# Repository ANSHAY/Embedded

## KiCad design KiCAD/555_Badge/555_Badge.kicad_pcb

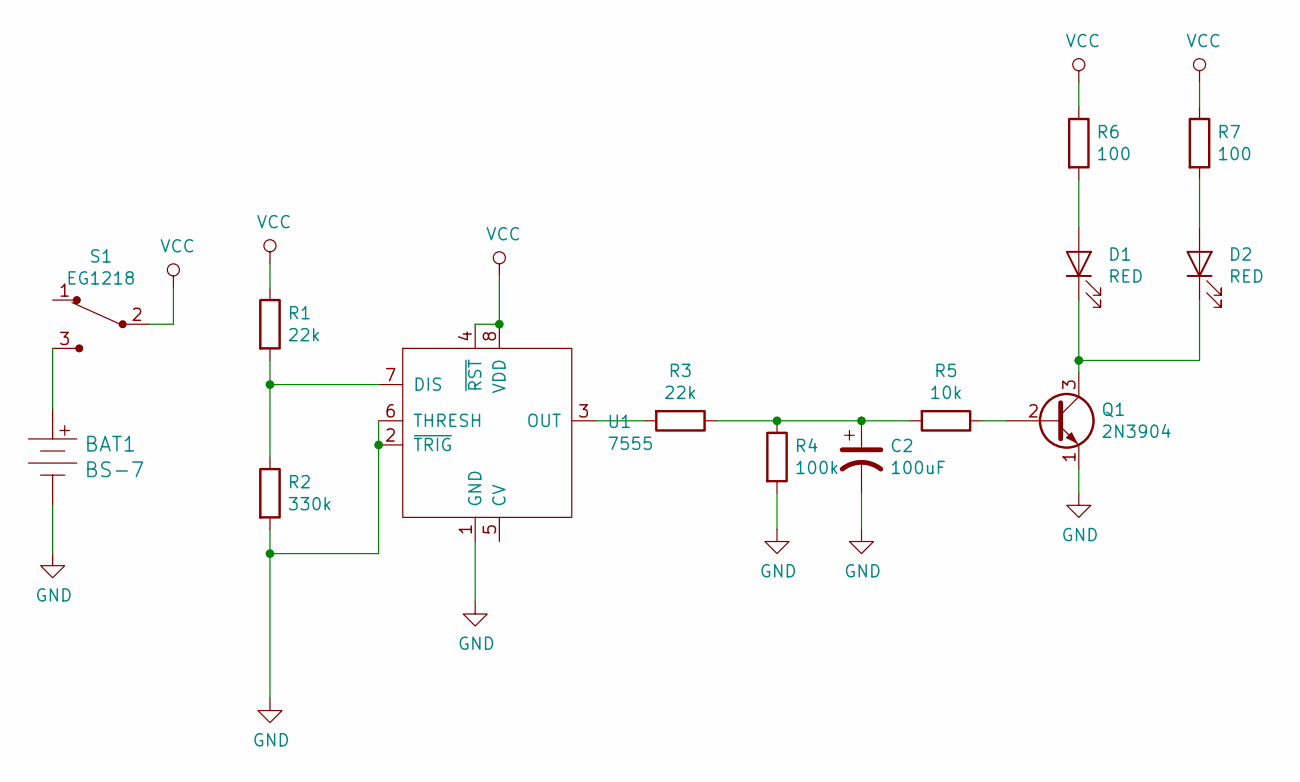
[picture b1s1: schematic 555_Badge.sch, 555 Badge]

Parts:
BAT1: BS-7; Battery_Holder_Coin_2032_BS-7; MPN BS-7; Digi-Key_PN BS-7-ND
C2: 100uF; CP_Radial_D6.3mm_P2.50mm
D1, D2: RED; LED_D3.0mm
Q1: 2N3904; TO-92-3
R1, R3: 22k; R_Axial_DIN0207_L6.3mm_D2.5mm_P7.62mm_Horizontal
R2: 330k; R_Axial_DIN0207_L6.3mm_D2.5mm_P7.62mm_Horizontal
R4: 100k; R_Axial_DIN0207_L6.3mm_D2.5mm_P7.62mm_Horizontal
R5: 10k; R_Axial_DIN0207_L6.3mm_D2.5mm_P7.62mm_Horizontal
R6, R7: 100; R_Axial_DIN0207_L6.3mm_D2.5mm_P7.62mm_Horizontal
S1: EG1218; Switch_Slide_11.6x4mm_EG1218; MPN EG1218; Digi-Key_PN EG1903-ND
U1: 7555; ICM7555-PDIP

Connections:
GND: BAT1.Neg, C2.2, Q1.1 (E), R2.2, R4.2, U1.1 (GND), U1.2 (~TRIG), U1.6 (THRESH)
unnamed: BAT1.Pos, S1.3
unnamed: C2.1, R3.1, R4.1, R5.2
unnamed: D1.1 (K), D2.1 (K), Q1.3 (C)
unnamed: D1.2 (A), R6.2
unnamed: D2.2 (A), R7.2
unnamed: Q1.2 (B), R5.1
unnamed: R1.2, R2.1, U1.7 (DIS)
unnamed: R3.2, U1.3 (OUT)
VCC: R1.1, R6.1, R7.1, S1.2, U1.4 (~RST), U1.8 (VDD)

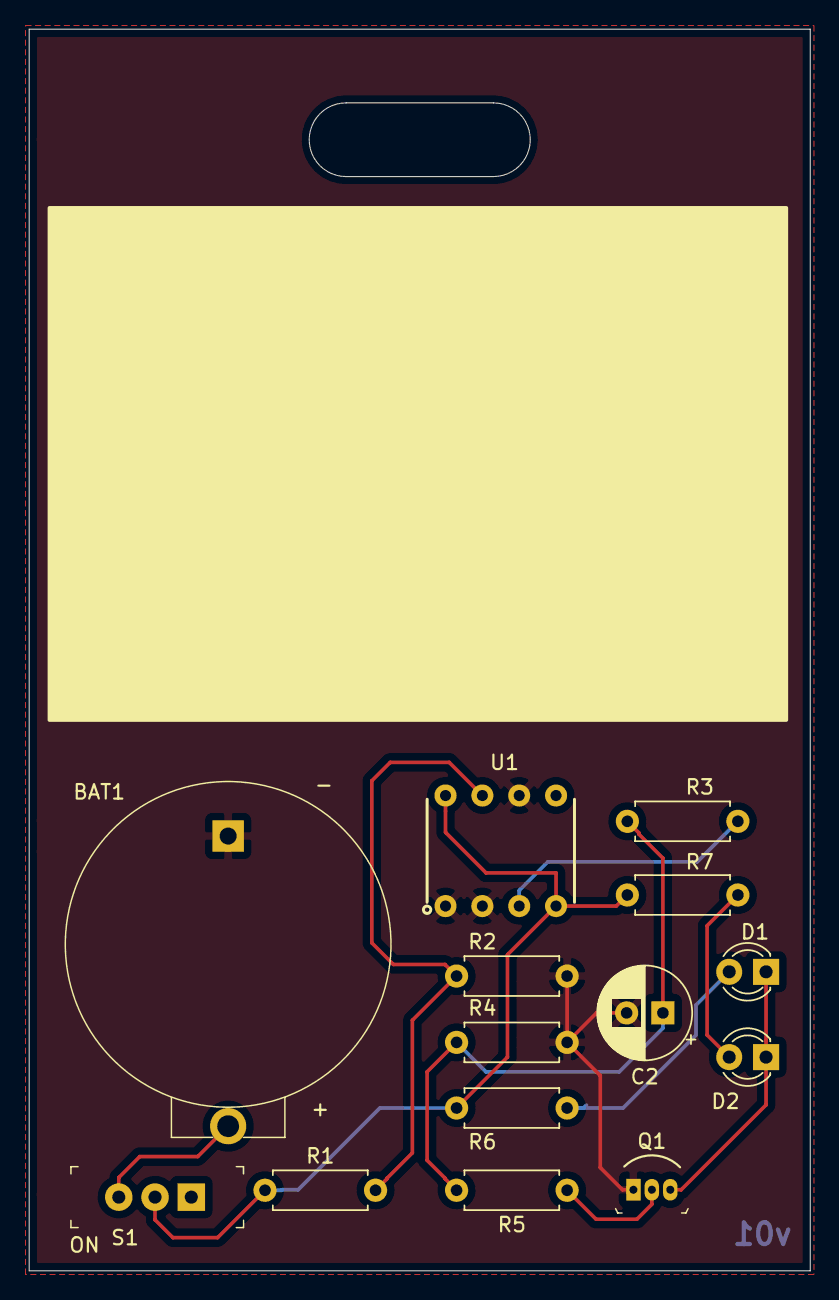
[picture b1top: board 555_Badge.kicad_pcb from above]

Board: 2 copper layers, 53.8 x 85.6 mm, 14 parts (0 on the bottom side), 10 nets.

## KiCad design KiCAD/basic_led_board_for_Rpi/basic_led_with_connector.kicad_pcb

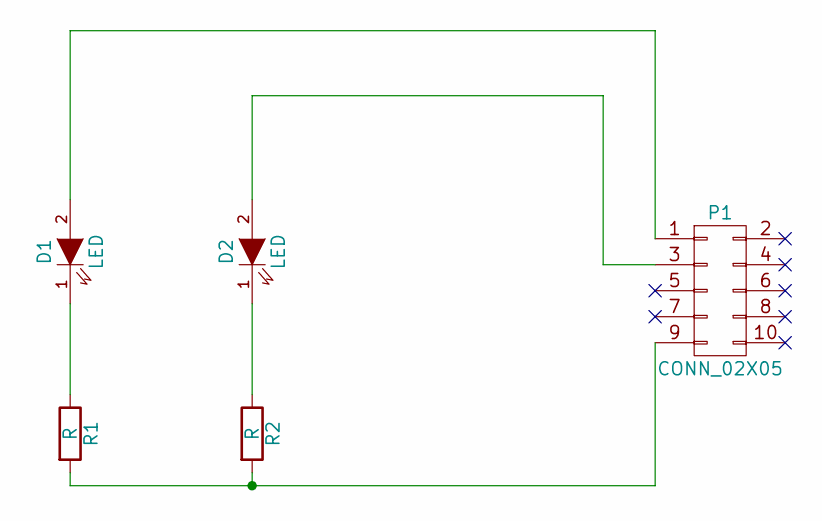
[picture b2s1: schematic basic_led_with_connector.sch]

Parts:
D1, D2: LED; LED-3MM
P1: CONN_02X05; Pin_Header_Straight_2x05
R1, R2: R; R_1206

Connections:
unnamed: D1.1 (K), R1.1
unnamed: D1.2 (A), P1.1
unnamed: D2.1 (K), R2.1
unnamed: D2.2 (A), P1.3
unnamed: P1.9, R1.2, R2.2

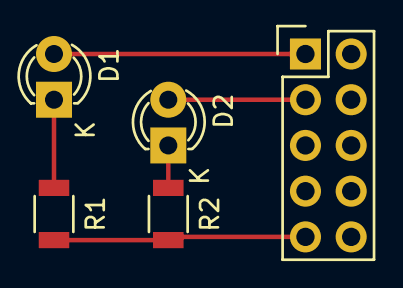
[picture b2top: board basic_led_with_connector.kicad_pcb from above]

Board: 2 copper layers, 5 parts (0 on the bottom side), 5 nets.

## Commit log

2019-02-04 Created Embedded Repo
    Created Embedded Repo for projects of embedded systems including Arduino, Eagle, IOT, LTSpice, TINATI, VHDL, Xilinx
2019-02-11 Created Arduino files
    Created keyboard, keyboard2, mototrpinwheel, magicball8, thereno
    description is inside the files
2019-03-27 Adds basic KiCAD schematics and PCB design
    Adds basic KiCAD schematics and PCB design
    which contains 2 LEDs, one for power status
    and other for control through GPIO. The PCB
    is designed to be attached to 10 GPIO pins
    of a Raspberry Pi through the 2x5 connector
2019-04-04 Completes 555 Badge
    Adds digikey libraries for project,
    adds pcb layout, gerber files, , bom
2019-04-05 Multiple changes
    Adds Fading LED schematic,
    moves XOR schematic to separate folder
2019-05-05 Create touch_sense.ino
    creates touch_sense which turns on an LED connected at pin 12 of arduino whenever the wire connected to pin 2 is touched. The capacitive sensing is done via pin 4 and 2 i.e. pin 4 is connected to pin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
2019-05-13 Updates on LED Blink
    Adds Cylon.
    Adds more ways to draw the design on LEDs
2019-05-18 Adds colorFade, siren and sirenwithpot
    Adds 3 new files.
    Description in comments.
2019-05-27 Added HappyBday tone generator
2019-07-15 Added and moved some projects
2021-01-08 Create LICENSE
2021-01-08 Removed VHDL files and updates license

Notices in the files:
KiCAD/555_Badge/555_Badge.kicad_pcb:
License: Creative Commons BY 4.0
KiCAD/555_Badge/555_Badge.sch:
creativecommons.org/licenses/by/4.0
License: CC BY 4.0
